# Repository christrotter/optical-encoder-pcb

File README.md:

# optical-encoder-pcb
A standalone pcb for Ploopy's optical encoder design.

# Status
I decided not to go ahead with this mainly because QMK doesn't really support quadrature and custom encoder drivers simultaneously (and why would they? - so bougie).
Also, the infrared leds are not in stock.

The theory was that I'd use the optical encoder for the mk20's 'ring' encoder, as it'd have less operating friction.

Anyways, I think the basics here would work - obviously I spent very little time on the pcb design.

# How it works
Pretty simple - until you get to the maths and code.

- a pair of infrared led/sensor combos aiming 'through' the scroll wheel
- matching resistors
- scroll wheel with a specific amount of holes to let light pass through
- lit up = analogue pin high; darkened = low

Basically you have power, ground, analog1, analog2.  When the LED light is interrupted by the wheel, the analog input goes low and thus the computer can do something about it.  Your polling code looks at the analog inputs and determines what to do based on the combinations of on/off received over a time period.

I also used a VIK connector cuz why not: https://github.com/sadekbaroudi/vik/

Fun sidenote - the silicone surface on their scroll wheel is actually a silicone ring (on Aliexpress, search 'silicone ring fish scale').

# Further reading
https://www.eeworldonline.com/rotary-encoders-part-1-optical-encoders/
https://github.com/ploopyco/qmk_firmware/blob/master/keyboards/ploopyco/common/opt_encoder_simple.c 
https://github.com/ploopyco/qmk_firmware/blob/master/keyboards/ploopyco/ploopyco.c#L101 
https://github.com/ploopyco/classic-trackball/tree/master/hardware/Electronics/Schematics

# My take on the design

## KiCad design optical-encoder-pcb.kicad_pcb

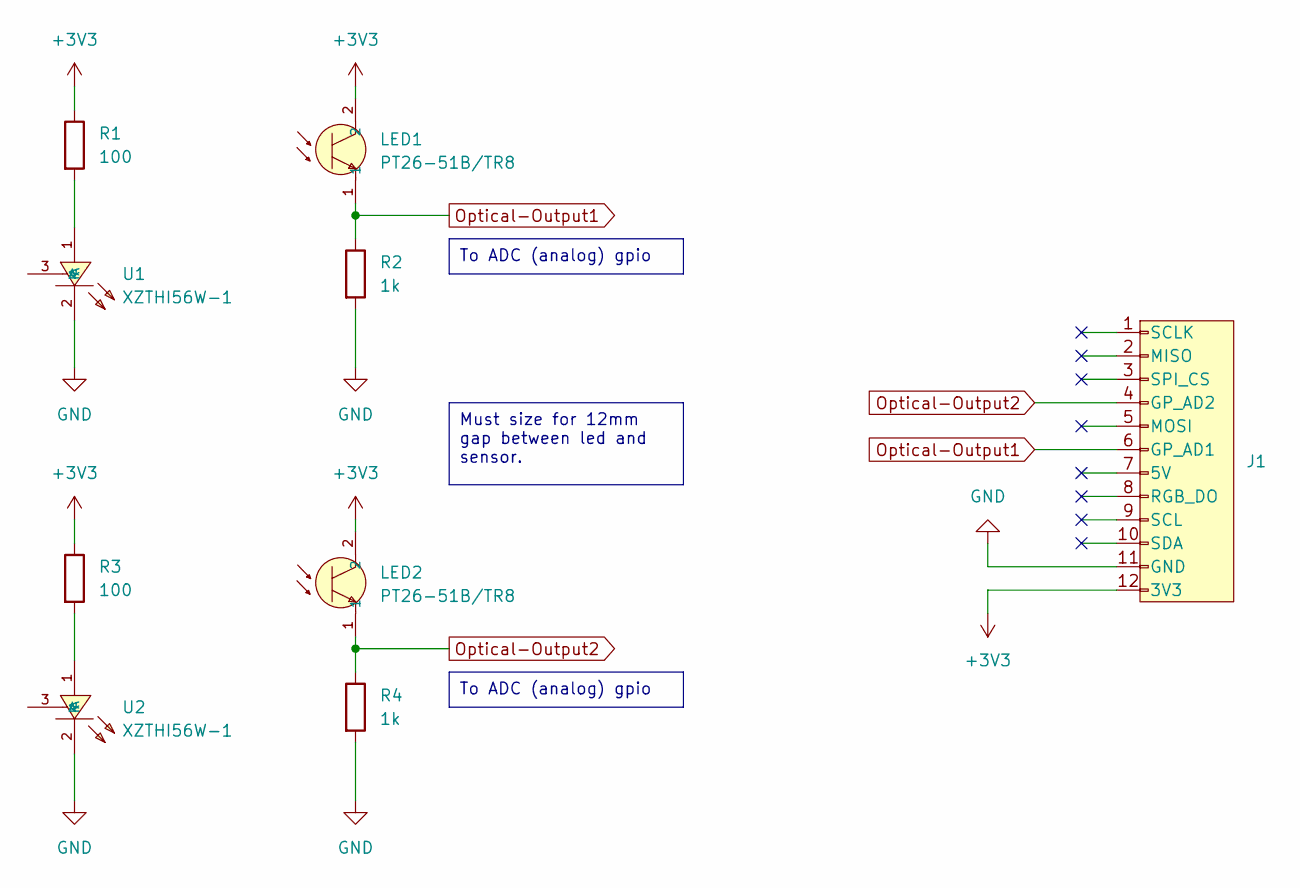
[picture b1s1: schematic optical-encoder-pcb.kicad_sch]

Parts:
J1: vik-module-connector; FPC-SMD_12P-P0.50_HCTL_XW05202-120R-00
LED1, LED2: PT26-51B/TR8; OPTO-SMD_PT26-51B-TR8; LCSC C55976
R1, R3: 100; R_0805_2012Metric
R2, R4: 1k; R_0805_2012Metric
U1, U2: XZTHI56W-1; LED-SMD_3P-L3.0-W2.5; LCSC C7158952

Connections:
+3V3: J1.12 (3V3), LED1.2, LED2.2, R1.1, R3.1
GND: J1.11 (GND), R2.2, R4.2, U1.2 (K), U2.2 (K)
unnamed: R1.2, U1.1 (A)
unnamed: R3.2, U2.1 (A)
Optical-Output1: J1.6 (GP_AD1), LED1.1, R2.1
Optical-Output2: J1.4 (GP_AD2), LED2.1, R4.1

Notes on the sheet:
To ADC (analog) gpio
Must size for 12mm gap between led and sensor.

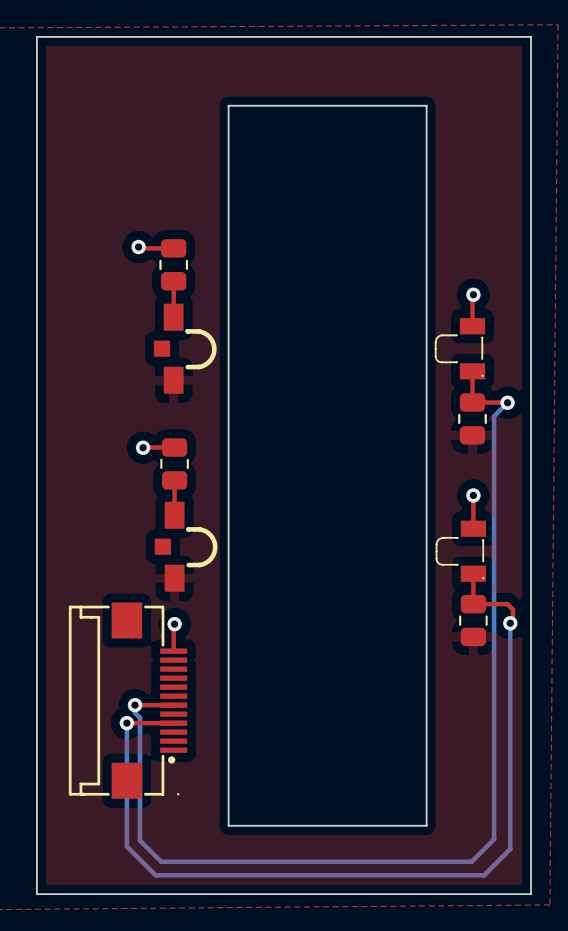
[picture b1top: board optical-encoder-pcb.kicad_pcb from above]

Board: 2 copper layers, 27.5 x 47.6 mm, 9 parts (0 on the bottom side), 6 nets.

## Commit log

2025-07-01 first revision, shelved
2025-07-01 updating readme
